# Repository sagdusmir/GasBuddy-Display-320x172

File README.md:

# OW GasBuddy Display and Home Assistant integration

This repository is a variation of the hardware used for https://github.com/sagdusmir/G32-Grill-Display-320x172-BT, and allows to use a OW GasBuddy without connecting it to a G32 gas grill. In case you own a 2nd or 3rd GasBuddy or your G32 broke down on you, this is for you.

Focus: **mobile, cloud-independent, G32-independent** GasBuddy display — no cloud login, no Otto Wilde servers, no G32. Gas weight is read from the scale over UART. Direct connection between GasBuddy and this device is required.

<br>Bare device during testing:<br>

<br>
<br>

# Table of Contents

1. [Features](#features)
   - [Implemented functionality](#implemented-functionality)  
   - [Limitations](#limitations)
3. [Hardware](#hardware)
   - [BOM](#bom)
   - [Component Details](#component-details)
   - [Wiring and Assembly](#wiring-and-assembly)
      - [Wiring](#wiring)
      - [Assembly](#assembly)
4. [Uploading the software to the ESP](#uploading-the-software-to-the-esp)
5. [Troubleshooting](#troubleshooting)
6. [Acknowledgments](#acknowledgments)
7. [Disclaimer](#disclaimer)

## Features

### Implemented functionality

- **Gas level** monitoring (requires OW GasBuddy)
- **Alarms** — visual indicator and optional buzzer for gas level and battery SOC. While either value is at or below its limit, the passive buzzer repeats the alert tone every 5 seconds. It stays quiet for the first 15 seconds after boot.
- Touchscreen configuration
  - tap the topmost status bar to get to the details screen
  - from the details screen you can launch the calibration wizard (which can be aborted in the if you need to)
  - the configuration wizard if fully contional using the device stand alone (no Home Assistant required)
- Multiple **color schemes** (predefined + easy to add your own)
- **Connection & status icons** (WiFi, battery SOC, Warning)
- **Optional battery monitoring** the state of charge (SOC) of a connected battery can be displayed
- **Optional Home Assistant** connectivity that exposes most of the measurements and allows confguring some settings of the device that can not be controlled using the UI on the device itself (min SOC level, min gas bottle level, color scheme, hide SOC, hide gas bottle level, screen powersave).

See [changelog.md](changelog.md).

### Limitations
* Volume level of the optional buzzer is a bit low.

### Missing
* 3d model for case / mount
* good weather for identifying any bugs that might arise during use

## Hardware
### BOM

| Component                                    | Qty | Source                                   | Costs            |
|----------------------------------------------|-----|------------------------------------------|------------------|
| ESP32 Dev Board                              | 1   | Amazon, AliExpress                       |   ~15€ - 20€     |
| Connector to original GasBuddy               | 1   | Alibaba                                  |    ~2€ - arm+leg |
| Battery                                      | 1   | AliExpress                               |    ~8€ - 12€     |
| Power Switch with Reverse Voltage Protection | 1   | somewhere online                         |    ~5€ - 10€     |
| Step-Up/Step-Down Voltage Regulator          | 1   | somewhere online                         |    ~8€ - 10€     |
| USB 5V 2A Boost Converter + Charger circuit  | 1   | AliExpress                               |     ~2€ - 5€     |
| USB-C Connector                              | 1   | Amazon, eBay, AliExpress                 |       ~2€        |
| 2 pin Wire Connectors                        | n   | Amazon, eBay, AliExpress                 |       ~2€        |
| Diode                                        | 3   | eBay, somewhere online                   |       ~1€        |
| Screws	                                      | 4   | hardware store, eBay, Amazon, AliExpress |       ~1€        |
| Buzzer	                                      | 1	  | Amazon, eBay, AliExpress                 |       ~1€        |
| some wires (soft silicone wire recommended)  | n   | AliExpress, Amazon, eBay                 |       ~2€        |
| Kapton tape or electrical tape (optional)    | ?   | AliExpress, Amazon, eBay                 |       ~0€        |
| strain relief (optional)                     | 1   | a friend with a 3d printer               |    a beer        |
| custom shield PCB (optional)                 | 1   | somewhere online                         |      ~10€        |
| Case (WORK IN PROGRESS)                      | 1   | a friend with a 3d printer               |    a beer        |
| zip ties (optional)                          | n   | your existing collection of zip ties     |       ~0€        |
| USB-C Connection Cable                       | 1   | your existing collection of cables       |       ~0€        |

### Component Details

* __ESP32 Dev Board__<br>
  You need a "__Waveshare ESP32-C6-Touch-LCD-1.47__". It is equipped with an ESP32-C6, WiFi, Bluetooth, a 320x172 Pixel 1.47" touchscreen, and everything you need. No additional memory card required. Attention: The non-touch version is a very different hardware.

* __Connector to original OW GasBuddy__<br>
  This is a "__LLT-M12-10004F3054__" (M12-4pin, female, UL2464 cable connector with thread lock) connector from LLT and might be hard to get. I found the manufacturer __Shenzhen Lilutong Electronic Technology Co., Ltd.__ on Alibaba. Feel free to <a href="https://www.sagdusmir.net" target="_blank"> contact me</a> in case you need one.
  <br>NOTE: I will stick to the colors used by OW. These connectors can be customised, and the the colors might not match, or can be swapped in comparison to the OW connector.
  <br>

* __Battery__
  A 3.7V LiPo/Li-Ion Battery (1 cell) will power the ESP32 Dev Board and the GasBuddy. Bigger is better and I went for 30000mAh. The GasBuddy alone consumes 145 mW of power.

* __Power Switch with Reverse Voltage Protection__<br>
  To minimize power draw, I am using a Pololu Mini Pushbutton Power Switch,Reverse Voltage Protection,LV (Pololu 2808) which should reduce power draw as much as possible. Unfortunately the module is a bit pricey.

* __Step-Up/Step-Down Voltage Regulator__<br>
  To provide power to the GasBuddy scale, I use a Pololu 5V Step-Up/Step-Down Voltage Regulator S7V8F5. This also has a shutdown input to turn power off.

* __5V 2A Boost Converter + Charger circuit__<br>
  I recommend using a cheap board that has an auto power-save feature. The one that I ultimately decided on goes under the name "Type-C USB 5V 2A Boost Converter Step-Up Power Module Lithium Battery Charging Protection Board LED Display USB Charger". The boost portion is actually not used because I wanted to keep it simple and have the SOC measurement working without adding another voltage divider for the voltage at the battery.
  Arduino PowerBoost 500C / 1000C modules seem to __NOT__ offer an automatic power-save feature, so this would completely drain the battery in a few days.
  <br>

* __USB-C Connector__<br>
  To power the charger circuit it is very helpful to have a male USB-C plug breakout board to supply power. The solder pads / USB port on the backside of my pcb were only used for power output and I found no accessible pads to provide power directly to the charger circuit.
  <br>

* __2 pin Wire Connectors__<br>
  I used a few micro JST1.25 2pin connectors (male + female) to keep things modular. At least the battery should be easy do disconnect so you do not have to solder the wires while it is connected.

* __Diode__<br>
  Schottky Diodes with a low voltage drop of 0.3-0.4V (e.g. 1N5819) to direct power flow.

* __Buzzer__<br>
  A __passive__ piezo buzzer.<br>Configured pins are GPIO5 amd GPIO6. The buzzer should be rather small (e.g. 12085 with ⌀12mm x 8.5mm or similar). 

* __strain relief__<br>
  An easy to print 3d model (fdm) that is fixed into place by two zip ties after pressing the GasBuddy cable into the channel on the backside. This is fully optional but should protect the cable connection to the pcb of the digital scale. (ugly color for demonstration purposes only)
  <br><br>

* __Custom PCB shield__<br>
  This greatly reduces the necessary wiring. The upcoming case will be tailored to the dev board with the custom PCB attached. Feel free to <a href="https://www.sagdusmir.net" target="_blank"> contact me</a> in case you need one of these.
  <br><br>

* __Case__<br>This is still a WORK IN PROGRESS
  
### Wiring and Assembly

#### Wiring
<br>Wiring when using the usb-c port for delivering power (the most basic option):
<br>
<br>Just connect the GasBuddy to the ESP32 Dev-Board. As always: the buzzer is optional.
<br>If you want to power this with a rechargeable battery, things get a bit more demanding and I came up with the following wiring suggestions...although there might be room for simplification.
<br>
<br>Wiring when using a rechargable battery:
<br>
<br>This is as complex as it gets but gives you the most freedom in arranging the components to your liking.
<br>
<br>Wiring when using a rechargable battery with the optional custom pcb:
<br>
<br>This is essentially the same as without the pcb - but reduces the wiring by a lot.

#### Assembly

__The anclosure is still a WORK IN PROGRESS__
<br>Upcoming, once the 3D model of the case is done.
<br>
<br>
<br>There a different options for mounting the Pololu S7V8F5. Connect it either by wire, between the boards, or on top of the shield. Make sure to have the soldering pads match the pads on the shield - you can simply flip it to reverse the pad order if you need to.

## Uploading the software to the ESP

### Prebuilt firmware

Each [GitHub Release](https://github.com/sagdusmir/GasBuddy-Display-320x172/releases/latest) includes compiled images with placeholder Wi-Fi, OTA, and Home Assistant values. The extra `.espbinpatch` suffix is the same firmware as a `.bin` — patch those secrets, then flash. Do not flash the download as-is.

| File | When to use |
|---|---|
| `*.factory.bin.espbinpatch` | First flash on a new or empty device (erases everything) |
| `*.ota.bin.espbinpatch` | Later updates if the device already works (keeps Wi-Fi and other saved settings) |

1. Download the matching file from the latest release.
2. Use the ESP Bin Patcher link in the release notes (preconfigured) in **Chrome or Edge**.
3. Choose the downloaded file on that page.
4. Fill in the replacements (Wi-Fi SSID, Wi-Fi password, OTA password, Home Assistant API key).
   For the API key, paste your Home Assistant / ESPHome `api.encryption.key` (the Base64 value) as **New**.
5. Click **Patch firmware**, connect the board via USB, then **Install patched firmware**.
   - Factory file: choose **Erase everything**.
   - OTA file: choose **Keep saved settings**.

### Compile from source

1. Install ESPHome CLI
   ```bash
   pip install esphome
   ```
2. Clone this repository and change directory into that folder
   ```bash
   git clone https://github.com/sagdusmir/GasBuddy-Display-320x172.git && cd GasBuddy-Display-320x172
   ```
3. Connect the ESP32-C6 1.47 Inch Display Development Board via USB
4. Compile and flash the software
   ```bash
   esphome run gasbuddy-display.yaml
   ```
   You may be asked how the connection should be established.

## Troubleshooting

1. If compiling and flashing the ESP32 succeeds, but the screen is looking distorted afterwards, skimply turn the power off and on agaoin. Pressing the BOOT button in the device is not sufficient.

2. If you get A LOT of strange syntax errors, try to clean up the configured build folder via
   ```bash
   esphome clean gasbuddy-display.yaml
   ```

## Acknowledgments
This project would not have been possible without the work of the community. Special thanks go to:

[tobsch/g32-investigations](https://github.com/tobsch/g32-investigations) (additional information about BLE and serial communication)

## Disclaimer
This is third-party software developed by the community and is not officially developed or supported by Otto Wilde GmbH. Use at your own risk.

__This project is provided for educational and experimental purposes only.__

All hardware designs, schematics, code, instructions, and documentation are offered AS IS without any warranty of any kind, express or implied.
YOU BUILD AND USE THIS AT YOUR OWN RISK.
The author(s) and any contributors are not responsible for any injury, death, property damage, fire, electrical shock, data loss, voided warranties, legal violations, or any other consequences — direct, indirect, incidental, or consequential — that may result from building, modifying, or using this project or any derivative work.
Always follow local electrical/safety/building codes.

If you're not experienced with mains voltage, high current, lithium batteries, lasers, moving parts, etc., consult a qualified professional before proceeding.
Proceed only if you accept full personal responsibility.

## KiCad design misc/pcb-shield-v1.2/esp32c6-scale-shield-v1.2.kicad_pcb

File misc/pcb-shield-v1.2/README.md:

# ESP32-C6 Scale Shield v1.2 (2026-11-01)

A 2-layer, 1.6 mm through-hole shield for the Waveshare **ESP32-C6-Touch-LCD-1.47**. It is based on v1.1, which has the on-board Pololu S7V8F5.

## Changes vs v1.1
1. **Header pads only for the ESP32 pins that are used.** Each pad stays at its exact original position (17.78 mm between the rows, 2.54 mm pitch, first pin 12.60 mm from the USB edge).
   - J1 (the VBUS row on the dev board's silkscreen): VBUS, GND, TXD, RXD, GPIO4, GPIO5, GPIO6 (pins 1-4 and 9-11).
   - J2 (the VBAT row): **VBAT only** (pin 1). One GND on J1 is enough electrically, so the extra GND pads are gone.
   - Removed: RST, IO1-3, 3V3, SCL, SDA, IO13, IO12, IO9, IO8, IO7 and both J2 GNDs.
2. **All four M2 mounting holes removed.** Each corner now has a **concave notch** of R2.5 mm around the dev board's post/hole centres, so the shield clears the case posts or standoffs under the dev board's mounting holes. The hole centres are 3.77 mm from the long edges and 2.75 mm from the short edges.
   - R2.5 clears a standoff up to about 5 mm across.
   - A larger notch would cut into the J1 GPIO6 pad, which sits 0.42 mm from the notch edge.
3. **Layout**
   - SCALE, CHG_IN and PSW pads moved to a column on the left edge, in the space freed from J2. They are **no longer under the S7V8F5**.
   - Labels are 0.8 mm text on both sides.
   - D1-D3 and R1/R2 moved 1.2 mm right.
   - GND pour on both layers.
   - Re-routed with no vias.
4. Silkscreen version is v1.2.

## Files
- `esp32c6-scale-shield-v1.2.kicad_pro / .kicad_pcb`: the KiCad 9 project. The netlist is in `tools/gen.py`.
- `gerbers.zip`: Gerbers and Excellon drill files (PTH; there are no NPTH holes now), ready for JLCPCB.
- `renders/top.png`, `renders/bottom.png`: 3D renders.
- `drc-report.txt`: **0 violations, 0 unconnected**.
- `tools/`: the generator (`gen.py`), the freerouting DSN/SES files, `ses_import.py`, and the Pololu dimension photo.

## Mounting
The shield sits **under** the dev board, display up. Viewed from the shield top with the USB edge up, J1 (VBUS) is on the right and J2 (VBAT) is on the left.
- Use female/stacking headers: a 1x4 and a 1x3 on J1, and a 1x1 on J2 (or a full 1x11 strip that only touches the populated holes).
- U1, the S7V8F5, is mounted piggyback on a 1x4 header near the USB end.
- Height: the buzzer is about 8 mm and the module stack about 6 mm, so the headers between the shield and the dev board need to be at least about 8-11 mm tall.

## Pin map
| Shield pad | ESP32 pin | Net / use |
|---|---|---|
| J1-1 | VBUS | D1, D2 anodes |
| J1-2 | GND | GND |
| J1-3 | TXD (GPIO16) | R2 to SCALE RX |
| J1-4 | RXD (GPIO17) | R1 to SCALE TX |
| J1-9 | GPIO4 | U1 SHDN (EN) |
| J1-10 | GPIO5 | BZ1 + |
| J1-11 | GPIO6 | BZ1 - |
| J2-1 | VBAT | PSW OUT, D3 anode |

## External pads (left column, 1.0 mm hole, 1.8 mm pad)
- **SCALE**: 5V (5V_SCALE), GND, RX (from ESP TXD through R2), TX (to ESP RXD through R1)
- **CHG_IN**: + (D1 cathode), - (GND)
- **PSW** (Pololu power switch): OUT (= VBAT), GND

## Circuit
- D1 1N5819: VBUS to CHG_IN+
- D2: VBUS to 5V_IN; D3: VBAT to 5V_IN
- U1 S7V8F5: VIN = 5V_IN, VOUT = 5V_SCALE, SHDN = GPIO4, GND
- R1 1k: RXD to SCALE_TX; R2 1k: TXD to SCALE_RX
- BZ1 piezo between GPIO5 and GPIO6

## BOM
| Ref | Qty | Part |
|---|---|---|
| D1-D3 | 3 | 1N5819, DO-41 |
| R1, R2 | 2 | 1 kOhm, axial 0207 |
| BZ1 | 1 | Passive piezo, 12 mm, 7.6 mm pin pitch |
| U1 | 1 | Pololu S7V8F5 (#2123) + 1x4 straight header |
| J1/J2 | - | Female/stacking headers: 1x4 + 1x3 + 1x1 |

## Design rules
- Tracks: 0.3 mm signal and 0.8 mm power, 0.2 mm clearance.
- Copper-to-edge clearance: 0.3 mm (it was 0.5 mm; lowered because of the notches).
- Silk text: 0.7-0.8 mm on most labels; the U1 pin labels stay at 0.6 mm because of the 2.54 mm pitch.

## Caveats and sources
- GPIO4 is also the onboard TF card's chip select (SD_CS).
- GPIO5 and GPIO6 are the QMI8658 IMU interrupt lines (INT1/INT2).
- Sources:
  - Waveshare wiki and official DXF: https://www.waveshare.com/wiki/ESP32-C6-Touch-LCD-1.47 and `ESP32-C6-Touch-LCD-1.47-2D3D.zip`
  - Pololu S7V8F5: https://www.pololu.com/product/2123

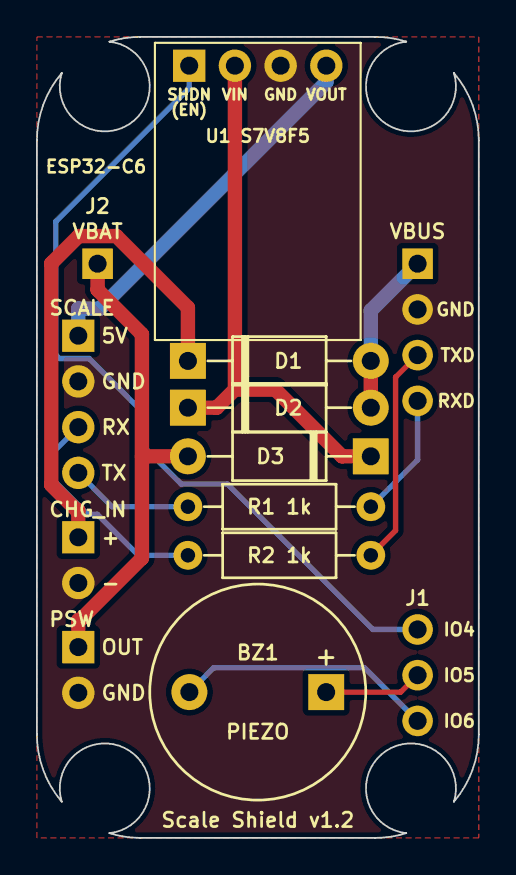
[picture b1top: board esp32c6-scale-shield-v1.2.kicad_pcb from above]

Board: 2 copper layers, 24.5 x 44.5 mm, 12 parts (0 on the bottom side), 13 nets.

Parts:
BZ1: Piezo 12mm
D1, D2, D3: 1N5819
J1, J2: ESP32 header (used pins)
J4: SCALE
J5: CHG_IN
J6: PSW
R1, R2: 1k
U1: Pololu S7V8F5

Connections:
5V_IN: D2.1, D3.1, U1.2
5V_SCALE: J4.1, U1.4
CHG_IN+: D1.1, J5.1
GND: J1.2, J4.2, J5.2, J6.2, U1.3
GPIO4: J1.9, U1.1
GPIO5: BZ1.1, J1.10
GPIO6: BZ1.2, J1.11
RXD: J1.4, R1.1
SCALE_RX: J4.3, R2.2
SCALE_TX: J4.4, R1.2
TXD: J1.3, R2.1
VBAT: D3.2, J2.1, J6.1
VBUS: D1.2, D2.2, J1.1
